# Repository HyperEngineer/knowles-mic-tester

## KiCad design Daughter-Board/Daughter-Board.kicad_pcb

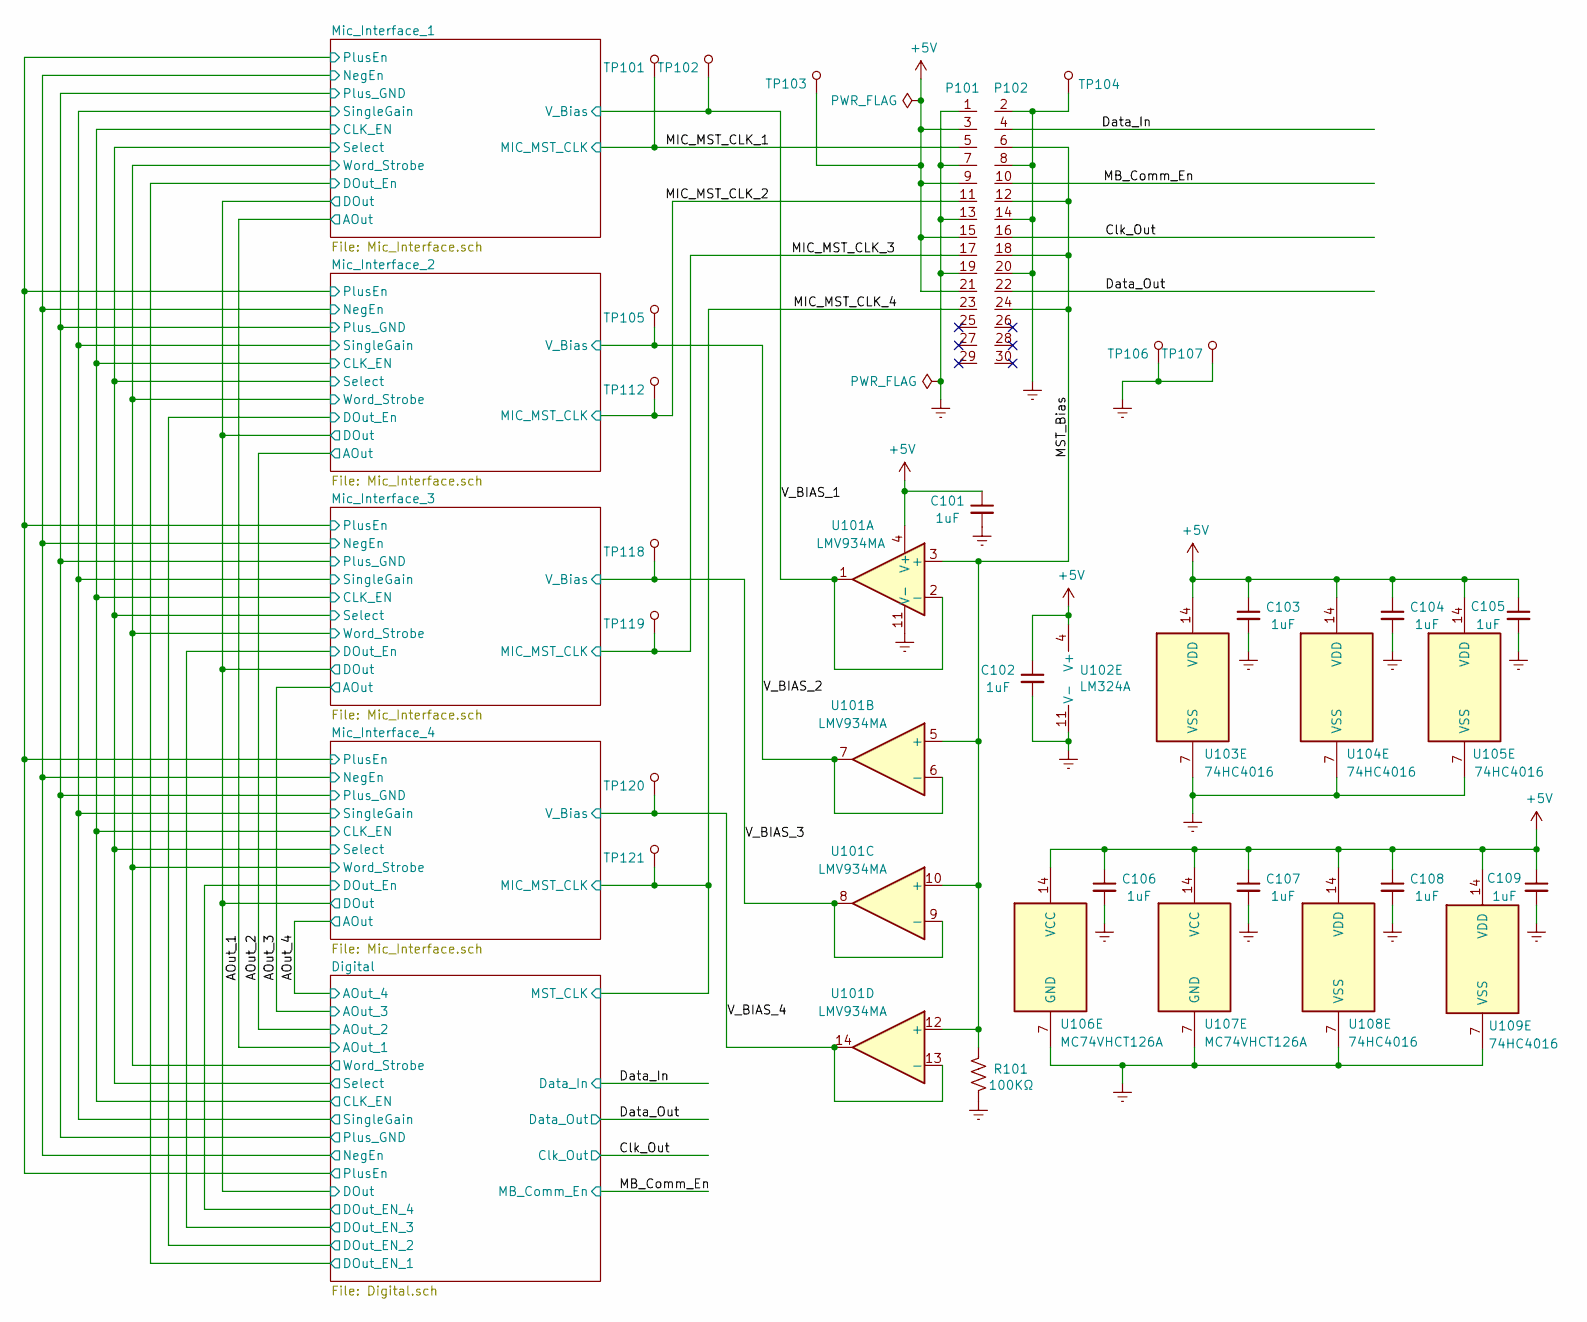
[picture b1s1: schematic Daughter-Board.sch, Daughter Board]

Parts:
C101, C102, C103, C104, C105, C106, C107, C108, C109: 1uF; C_0805_2012Metric; DigiKey # 478-12854-1-ND
P101: EdgeConn; Component_Side_Edge_Conn_30
P102: EdgeConn; Solder_Side_Edge_Conn_30
R101: 100KΩ; R_0805_2012Metric; DigiKey # 541-4173-1-ND
TP101, TP102, TP103, TP104, TP105, TP106, TP107, TP112, TP118, TP119, TP120, TP121: 5000; TestPoint_Pad_D1.0mm; MPN 5000; Digi-Key_PN 36-5000-ND
U101: LMV934MA; TSSOP-14_4.4x5mm_P0.65mm; Mouser # 926-LMV934MA/NOPB
U102: LM324A; TSSOP-14_4.4x5mm_P0.65mm
U103, U104, U105, U108, U109: 74HC4016; SOIC-14_3.9x8.7mm_P1.27mm; DigiKey # 296-CD74HC4016MTCT-ND
U106: MC74VHCT126A; SOIC-14_3.9x8.7mm_P1.27mm; Mouser # 771-74VHCT126D118
U107: MC74VHCT126A; TSSOP-14_4.4x5mm_P0.65mm; Mouser # 771-74VHCT126D118

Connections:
+5V: C101.1, C102.1, C103.1, C104.1, C105.1, C106.1, C107.1, C108.1, C109.1, P101.3, P101.9, P101.15, P101.21, TP103.1, U101.4 (V+), U102.4 (V+), U103.14 (VDD), U104.14 (VDD), U105.14 (VDD), U106.14 (VCC), U107.14 (VCC), U108.14 (VDD), U109.14 (VDD); also elsewhere on the board
/AOut_2: U102.7; also elsewhere on the board
/AOut_3: U102.14; also elsewhere on the board
/AOut_4: U102.8; also elsewhere on the board
/Clk_Out: P102.16; also elsewhere on the board
/Data_In: P102.4; also elsewhere on the board
/Data_Out: P102.22; also elsewhere on the board
/Digital/CLK_EN: U107.4, U107.10, U107.13; also elsewhere on the board
/Digital/SingleGain: U105.5, U105.6, U105.12; also elsewhere on the board
/MB_Comm_En: P102.10; also elsewhere on the board
/MIC_MST_CLK_1: P101.5, TP101.1; also elsewhere on the board
/MIC_MST_CLK_2: P101.11, TP112.1, U107.5
/MIC_MST_CLK_3: P101.17, TP119.1, U107.9
/MIC_MST_CLK_4: P101.23, TP121.1, U107.12; also elsewhere on the board
/MST_Bias: P102.6, P102.12, P102.18, P102.24, R101.1, U101.3 (+), U101.5 (+), U101.10 (+), U101.12 (+)
/V_BIAS_1: TP102.1, U101.1, U101.2 (-); also elsewhere on the board
/V_BIAS_2: TP105.1, U101.6 (-), U101.7; also elsewhere on the board
/V_BIAS_3: TP118.1, U101.8, U101.9 (-); also elsewhere on the board
/V_BIAS_4: TP120.1, U101.13 (-), U101.14; also elsewhere on the board
GNDREF: C101.2, C102.2, C103.2, C104.2, C105.2, C106.2, C107.2, C108.2, C109.2, P101.1, P101.7, P101.13, P101.19, P102.2, P102.8, P102.14, P102.20, R101.2, TP104.1, TP106.1, TP107.1, U101.11 (V-), U102.11 (V-), U103.7 (VSS), U104.7 (VSS), U105.3, U105.7 (VSS), U105.9, U105.10, U106.7 (GND), U107.7 (GND), U108.7 (VSS), U109.7 (VSS); also elsewhere on the board
unnamed 50: U107.6; also elsewhere on the board
unnamed 54: U107.11; also elsewhere on the board
unnamed 58: U107.8; also elsewhere on the board
unnamed 70: U102.5 (+); also elsewhere on the board
unnamed 72: U105.4; also elsewhere on the board
unnamed 73: U102.6 (-); also elsewhere on the board
unnamed 74: U102.10 (+); also elsewhere on the board
unnamed 76: U105.8; also elsewhere on the board
unnamed 77: U102.9 (-); also elsewhere on the board
unnamed 78: U102.12 (+); also elsewhere on the board
unnamed 80: U105.11; also elsewhere on the board
unnamed 81: U102.13 (-); also elsewhere on the board

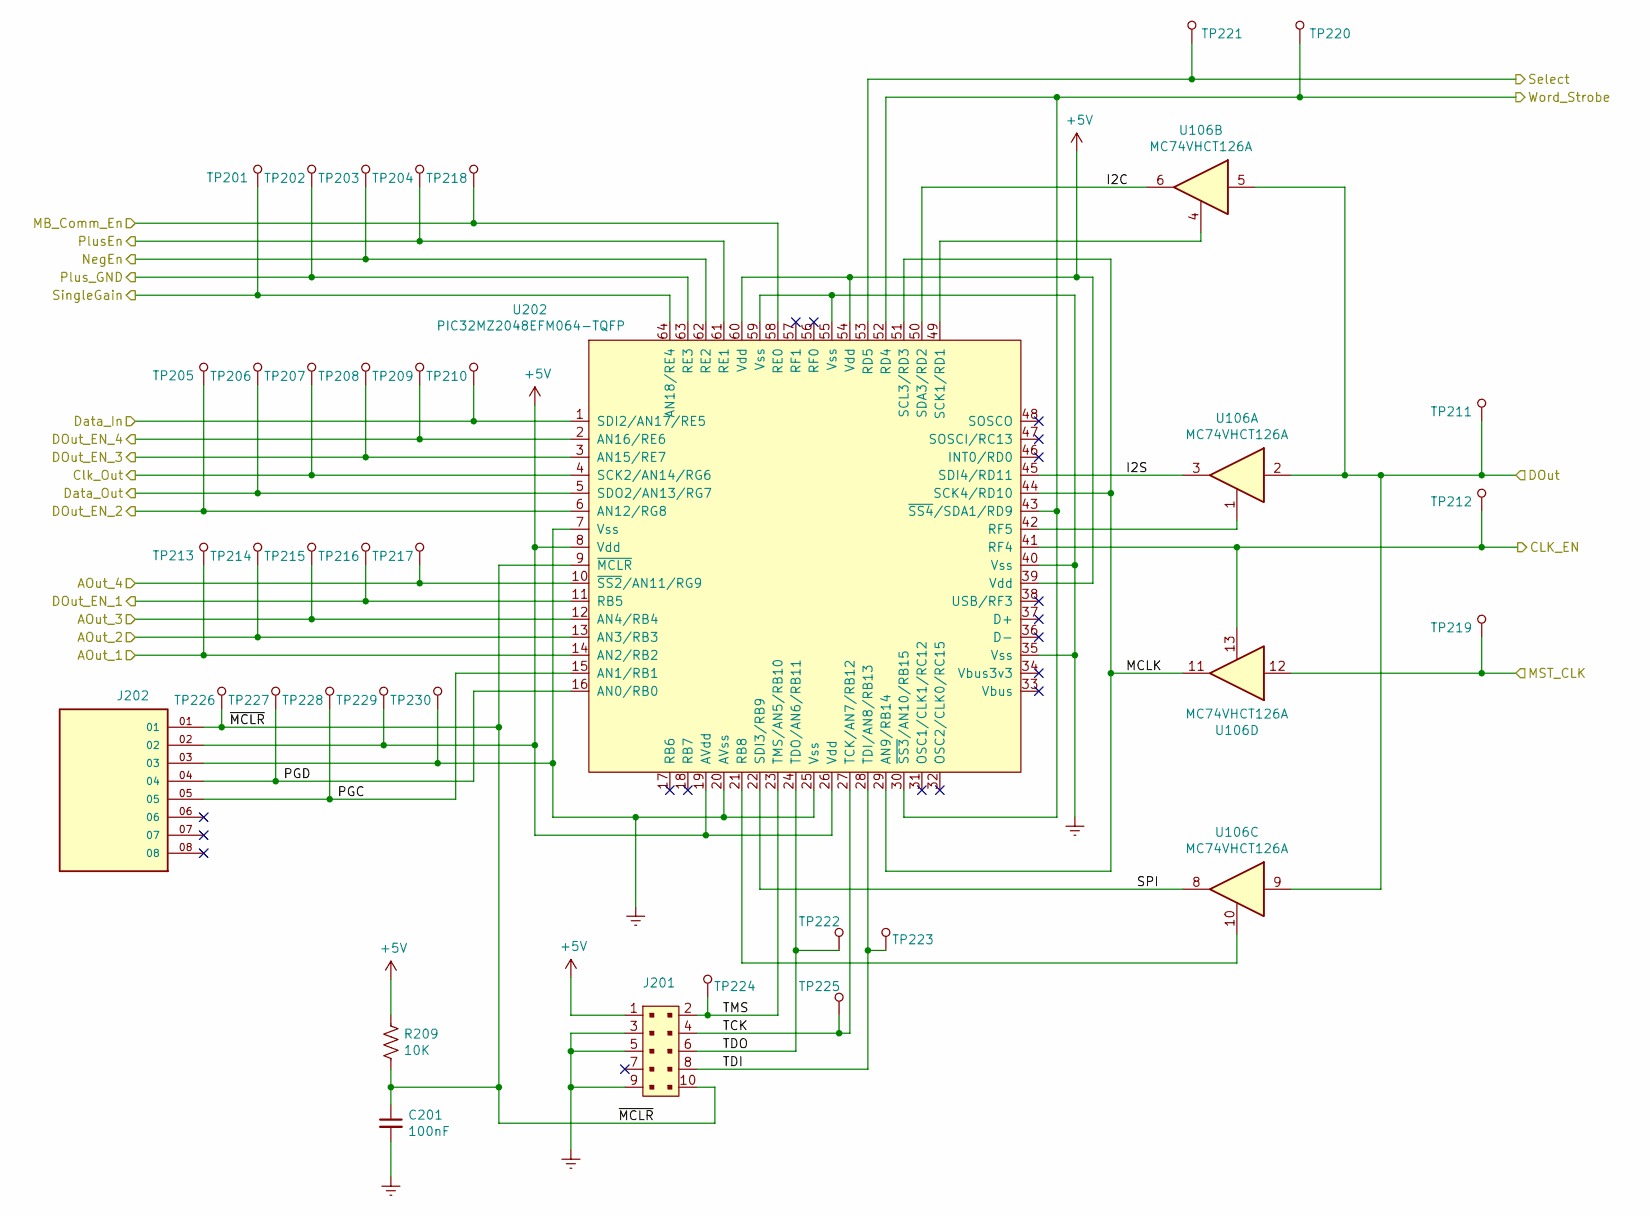
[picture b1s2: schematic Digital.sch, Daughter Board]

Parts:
C201: 100nF; C_0805_2012Metric; DigiKey # 476-12852-1-ND
J201: 302-S101; PinHeader_2x5_P2.54mm_Drill1.2mm; DigiKey # ED1543-ND
J202: TSW-108-09-G-S-RA; SAMTEC_TSW-108-09-G-S-RA; DigiKey # TSW-108-09-G-S-RA-ND
R209: 10K; R_0805_2012Metric; DigiKey # 541-CRCW12063K90FKEACCT-ND
TP201, TP202, TP203, TP204, TP205, TP206, TP207, TP208, TP209, TP210, TP211, TP212, TP213, TP214, TP215, TP216, TP217, TP218, TP219, TP220, TP221, TP222, TP223, TP224, TP225, TP226, TP227, TP228, TP229, TP230: 5000; TestPoint_Pad_D1.0mm; MPN 5000; Digi-Key_PN 36-5000-ND
U106: MC74VHCT126A; SOIC-14_3.9x8.7mm_P1.27mm
U202: PIC32MZ2048EFM064-TQFP; TQFP-64_10x10mm_P0.5mm; DigiKey # PIC32MZ2048EFM064-E/PT-ND

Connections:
+5V: J201.1, J202.02, R209.1, TP229.1, U202.8 (Vdd), U202.19 (AVdd), U202.26 (Vdd), U202.39 (Vdd), U202.54 (Vdd), U202.60 (Vdd); also elsewhere on the board
/AOut_1: TP213.1, U202.14 (AN2/RB2); also elsewhere on the board
/AOut_2: TP214.1, U202.13 (AN3/RB3); also elsewhere on the board
/AOut_3: TP215.1, U202.12 (AN4/RB4); also elsewhere on the board
/AOut_4: TP217.1, U202.10 (~SS2~/AN11/RG9); also elsewhere on the board
/Clk_Out: TP207.1, U202.4 (SCK2/AN14/RG6); also elsewhere on the board
/Data_In: TP210.1, U202.1 (SDI2/AN17/RE5); also elsewhere on the board
/Data_Out: TP206.1, U202.5 (SDO2/AN13/RG7); also elsewhere on the board
/Digital/CLK_EN: TP212.1, U106.13, U202.41 (RF4); also elsewhere on the board
/Digital/DOut: TP211.1, U106.2, U106.5, U106.9; also elsewhere on the board
/Digital/DOut_EN_1: TP216.1, U202.11 (RB5); also elsewhere on the board
/Digital/DOut_EN_2: TP205.1, U202.6 (AN12/RG8); also elsewhere on the board
/Digital/DOut_EN_3: TP208.1, U202.3 (AN15/RE7); also elsewhere on the board
/Digital/DOut_EN_4: TP209.1, U202.2 (AN16/RE6); also elsewhere on the board
/Digital/I2C: U106.6, U202.50 (SDA3/RD2)
/Digital/I2S: U106.3, U202.45 (SDI4/RD11)
/Digital/MCLK: U106.11, U202.29 (AN9/RB14), U202.44 (SCK4/RD10), U202.51 (SCL3/RD3)
/Digital/NegEn: TP203.1, U202.62 (RE2); also elsewhere on the board
/Digital/PGC: J202.05, TP228.1, U202.15 (AN1/RB1)
/Digital/PGD: J202.04, TP227.1, U202.16 (AN0/RB0)
/Digital/SPI: U106.8, U202.22 (SDI3/RB9)
/Digital/Select: TP221.1, U202.53 (RD5); also elsewhere on the board
/Digital/SingleGain: TP201.1, U202.64 (AN18/RE4); also elsewhere on the board
/Digital/TCK: J201.4, TP225.1, U202.27 (TCK/AN7/RB12)
/Digital/TDI: J201.8, TP223.1, U202.28 (TDI/AN8/RB13)
/Digital/TDO: J201.6, TP222.1, U202.24 (TDO/AN6/RB11)
/Digital/TMS: J201.2, TP224.1, U202.23 (TMS/AN5/RB10)
/Digital/Word_Strobe: TP220.1, U202.30 (~SS3~/AN10/RB15), U202.43 (~SS4~/SDA1/RD9), U202.52 (RD4); also elsewhere on the board
/Digital/~MCLR: C201.1, J201.10, J202.01, R209.2, TP226.1, U202.9 (~MCLR)
/MB_Comm_En: TP218.1, U202.58 (RE0); also elsewhere on the board
/MIC_MST_CLK_4: TP219.1, U106.12; also elsewhere on the board
GNDREF: C201.2, J201.3, J201.5, J201.9, J202.03, TP230.1, U202.7 (Vss), U202.20 (AVss), U202.25 (Vss), U202.35 (Vss), U202.40 (Vss), U202.55 (Vss), U202.59 (Vss); also elsewhere on the board
unnamed: U106.1, U202.42 (RF5)
unnamed: U106.4, U202.49 (SCK1/RD1)
unnamed: U106.10, U202.21 (RB8)
PlusEn: TP204.1, U202.61 (RE1); also elsewhere on the board
Plus_GND: TP202.1, U202.63 (RE3); also elsewhere on the board

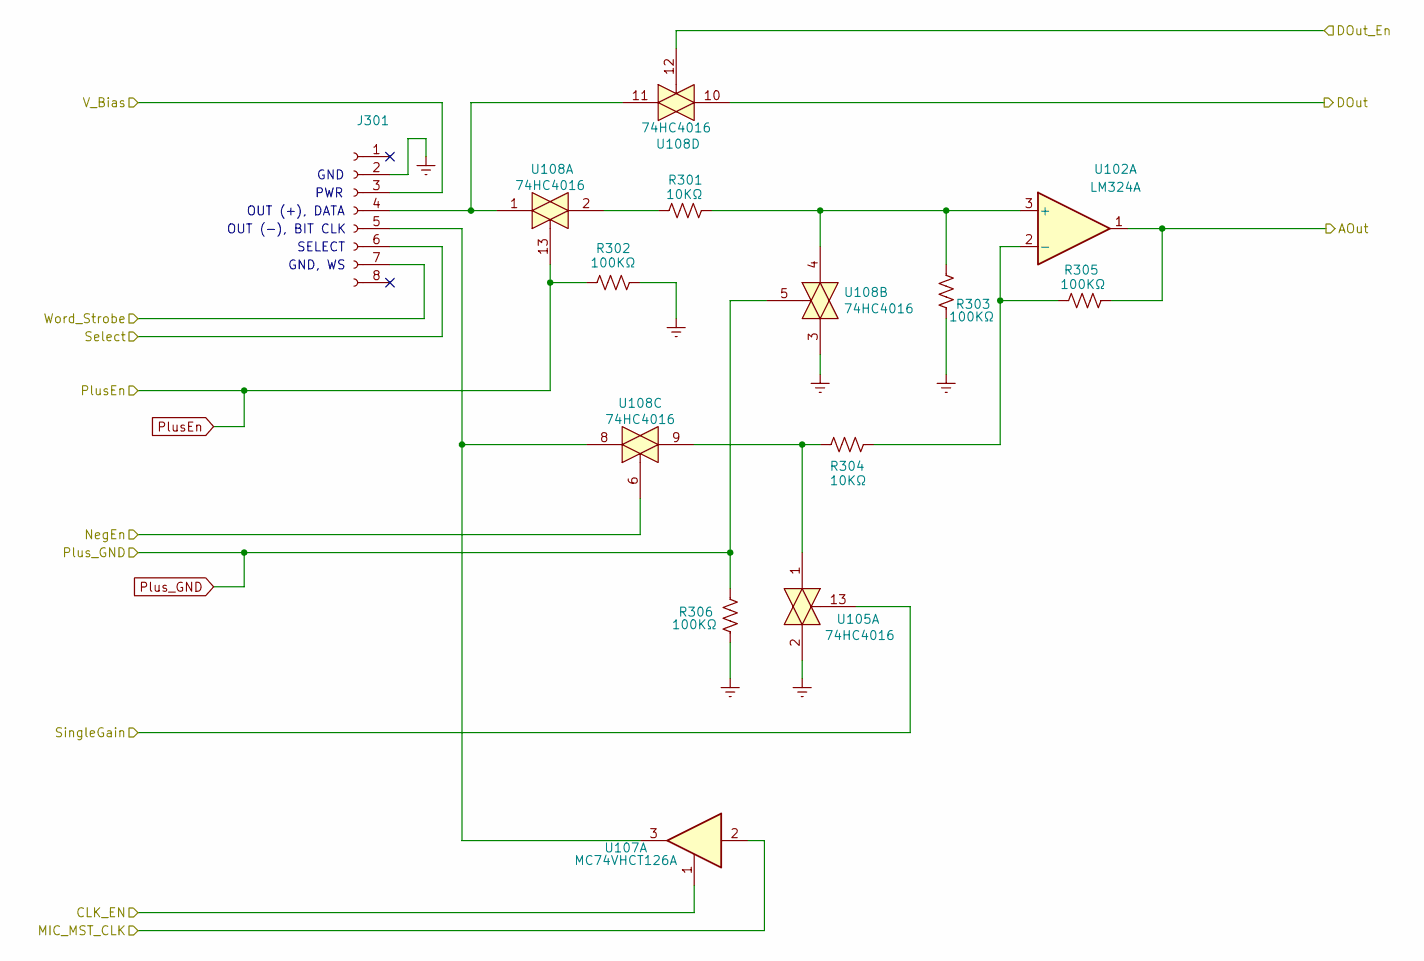
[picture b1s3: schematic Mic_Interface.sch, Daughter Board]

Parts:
J301: Conn_01x08_0.5mm_Female_Kyocera; Kyocera_6288; Digi-Key 478-5454-1-ND
R301, R304: 10KΩ; R_0805_2012Metric; DigiKey # 541-3983-1-ND
R302: 100KΩ; R_0805_2012Metric; DigiKey # 5414173-1-ND
R303, R305: 100KΩ; R_0805_2012Metric; DigiKey # 541-4173-1-ND
R306: 100KΩ; R_0805_2012Metric
U102: LM324A; TSSOP-14_4.4x5mm_P0.65mm
U105, U108: 74HC4016; SOIC-14_3.9x8.7mm_P1.27mm
U107: MC74VHCT126A; SOIC-14_3.9x8.7mm_P1.27mm; Mouser # 771-74VHCT126D118

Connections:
/AOut_1: R305.1, U102.1; also elsewhere on the board
/AOut_2: U102.7; also elsewhere on the board
/AOut_3: U102.14; also elsewhere on the board
/AOut_4: U102.8; also elsewhere on the board
/Digital/CLK_EN: U107.1, U107.4, U107.10, U107.13; also elsewhere on the board
/Digital/DOut: U108.10; also elsewhere on the board
/Digital/DOut_EN_1: U108.12; also elsewhere on the board
/Digital/NegEn: U108.6; also elsewhere on the board
/Digital/Select: J301.6; also elsewhere on the board
/Digital/SingleGain: U105.5, U105.6, U105.12, U105.13; also elsewhere on the board
/Digital/Word_Strobe: J301.7; also elsewhere on the board
/MIC_MST_CLK_1: U107.2; also elsewhere on the board
/MIC_MST_CLK_2: U107.5; also elsewhere on the board
/MIC_MST_CLK_3: U107.9; also elsewhere on the board
/MIC_MST_CLK_4: U107.12; also elsewhere on the board
/V_BIAS_1: J301.3; also elsewhere on the board
GNDREF: J301.2, R302.1, R303.1, R306.1, U105.2, U105.3, U105.9, U105.10, U108.3; also elsewhere on the board
unnamed: J301.4, U108.1, U108.11
unnamed: J301.5, U107.3, U108.8
unnamed 50: U107.6; also elsewhere on the board
unnamed 54: U107.11; also elsewhere on the board
unnamed 58: U107.8; also elsewhere on the board
unnamed: R301.1, R303.2, U102.3 (+), U108.4
unnamed: R301.2, U108.2
unnamed: R304.1, U105.1, U108.9
unnamed: R304.2, R305.2, U102.2 (-)
unnamed 70: U102.5 (+); also elsewhere on the board
unnamed 72: U105.4; also elsewhere on the board
unnamed 73: U102.6 (-); also elsewhere on the board
unnamed 74: U102.10 (+); also elsewhere on the board
unnamed 76: U105.8; also elsewhere on the board
unnamed 77: U102.9 (-); also elsewhere on the board
unnamed 78: U102.12 (+); also elsewhere on the board
unnamed 80: U105.11; also elsewhere on the board
unnamed 81: U102.13 (-); also elsewhere on the board
PlusEn: R302.2, U108.13; also elsewhere on the board
Plus_GND: R306.2, U108.5; also elsewhere on the board

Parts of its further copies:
J401, J501, J601: Conn_01x08_0.5mm_Female_Kyocera; Kyocera_6288; Digi-Key 478-5454-1-ND
R401, R404, R501, R504, R601, R604: 10KΩ; R_0805_2012Metric; DigiKey # 541-3983-1-ND
R402, R502, R602: 100KΩ; R_0805_2012Metric; DigiKey # 5414173-1-ND
R403, R405, R503, R505, R603, R605: 100KΩ; R_0805_2012Metric; DigiKey # 541-4173-1-ND
R406, R506, R606: 100KΩ; R_0805_2012Metric

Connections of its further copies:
/AOut_2: R405.1; also elsewhere on the board
/AOut_3: R605.1; also elsewhere on the board
/AOut_4: R505.1; also elsewhere on the board
/Digital/Select: J401.6, J501.6, J601.6; also elsewhere on the board
/Digital/Word_Strobe: J401.7, J501.7, J601.7; also elsewhere on the board
/V_BIAS_2: J401.3; also elsewhere on the board
/V_BIAS_3: J601.3; also elsewhere on the board
/V_BIAS_4: J501.3; also elsewhere on the board
GNDREF: J401.2, J501.2, J601.2, R402.1, R403.1, R406.1, R502.1, R503.1, R506.1, R602.1, R603.1, R606.1; also elsewhere on the board
unnamed 49: J401.4; also elsewhere on the board
unnamed 50: J401.5; also elsewhere on the board
unnamed 53: J501.4; also elsewhere on the board
unnamed 54: J501.5; also elsewhere on the board
unnamed 57: J601.4; also elsewhere on the board
unnamed 58: J601.5; also elsewhere on the board
unnamed 70: R401.1, R403.2; also elsewhere on the board
unnamed 71: R401.2; also elsewhere on the board
unnamed 72: R404.1; also elsewhere on the board
unnamed 73: R404.2, R405.2; also elsewhere on the board
unnamed 74: R501.1, R503.2; also elsewhere on the board
unnamed 75: R501.2; also elsewhere on the board
unnamed 76: R504.1; also elsewhere on the board
unnamed 77: R504.2, R505.2; also elsewhere on the board
unnamed 78: R601.1, R603.2; also elsewhere on the board
unnamed 79: R601.2; also elsewhere on the board
unnamed 80: R604.1; also elsewhere on the board
unnamed 81: R604.2, R605.2; also elsewhere on the board
PlusEn: R402.2, R502.2, R602.2; also elsewhere on the board
Plus_GND: R406.2, R506.2, R606.2; also elsewhere on the board

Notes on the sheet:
PWR
GND
OUT (+), DATA
OUT (-), BIT CLK
SELECT
GND, WS

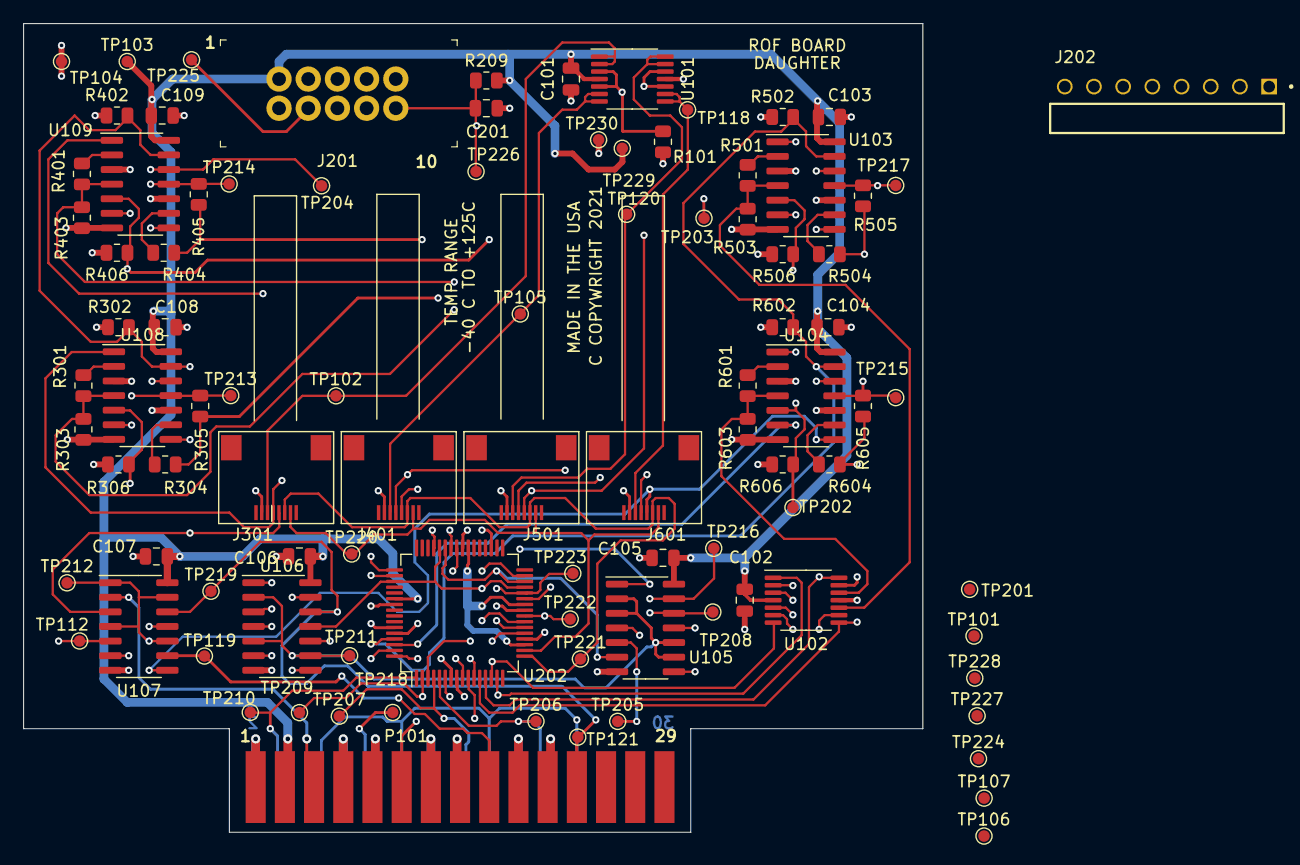
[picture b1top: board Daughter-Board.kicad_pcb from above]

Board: 4 copper layers, 78.2 x 70.4 mm, 96 parts (1 on the bottom side), 69 nets.

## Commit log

2021-10-13 changed n-type MOSFETs to cd4016 plus minor changes
2021-12-02 Remove the backup files
2021-12-02 Add test points to Digital and Daughter-Board schematics
2021-12-02 Add .gitignore file
2021-12-02 Really add Excel BoM file.
2021-12-02 Update component footprint for U102E.
2021-12-02 Add DigiKey # or Mouser # to component info, update footprintinfo for 14 and 20 pin devices.
2021-12-02 Add .gitignore to upper level folder, add *.odt to sub folder .gitignore
2021-12-13 Corrected analog gain switch position.
    Analog gain switch was across the feedback resistor. It is changed to grounding of the - input resistor to the op amp.
2021-12-18 Remove LEDs and circuitry, update J201 footprint to have a square pad on pin 1.]
2021-12-20 Add connector for PICkit to MCU interface.
    In the process of adding the PICkit connector some control lines had to be moved.
2021-12-28 Modify schematic to recover PCB layout.
